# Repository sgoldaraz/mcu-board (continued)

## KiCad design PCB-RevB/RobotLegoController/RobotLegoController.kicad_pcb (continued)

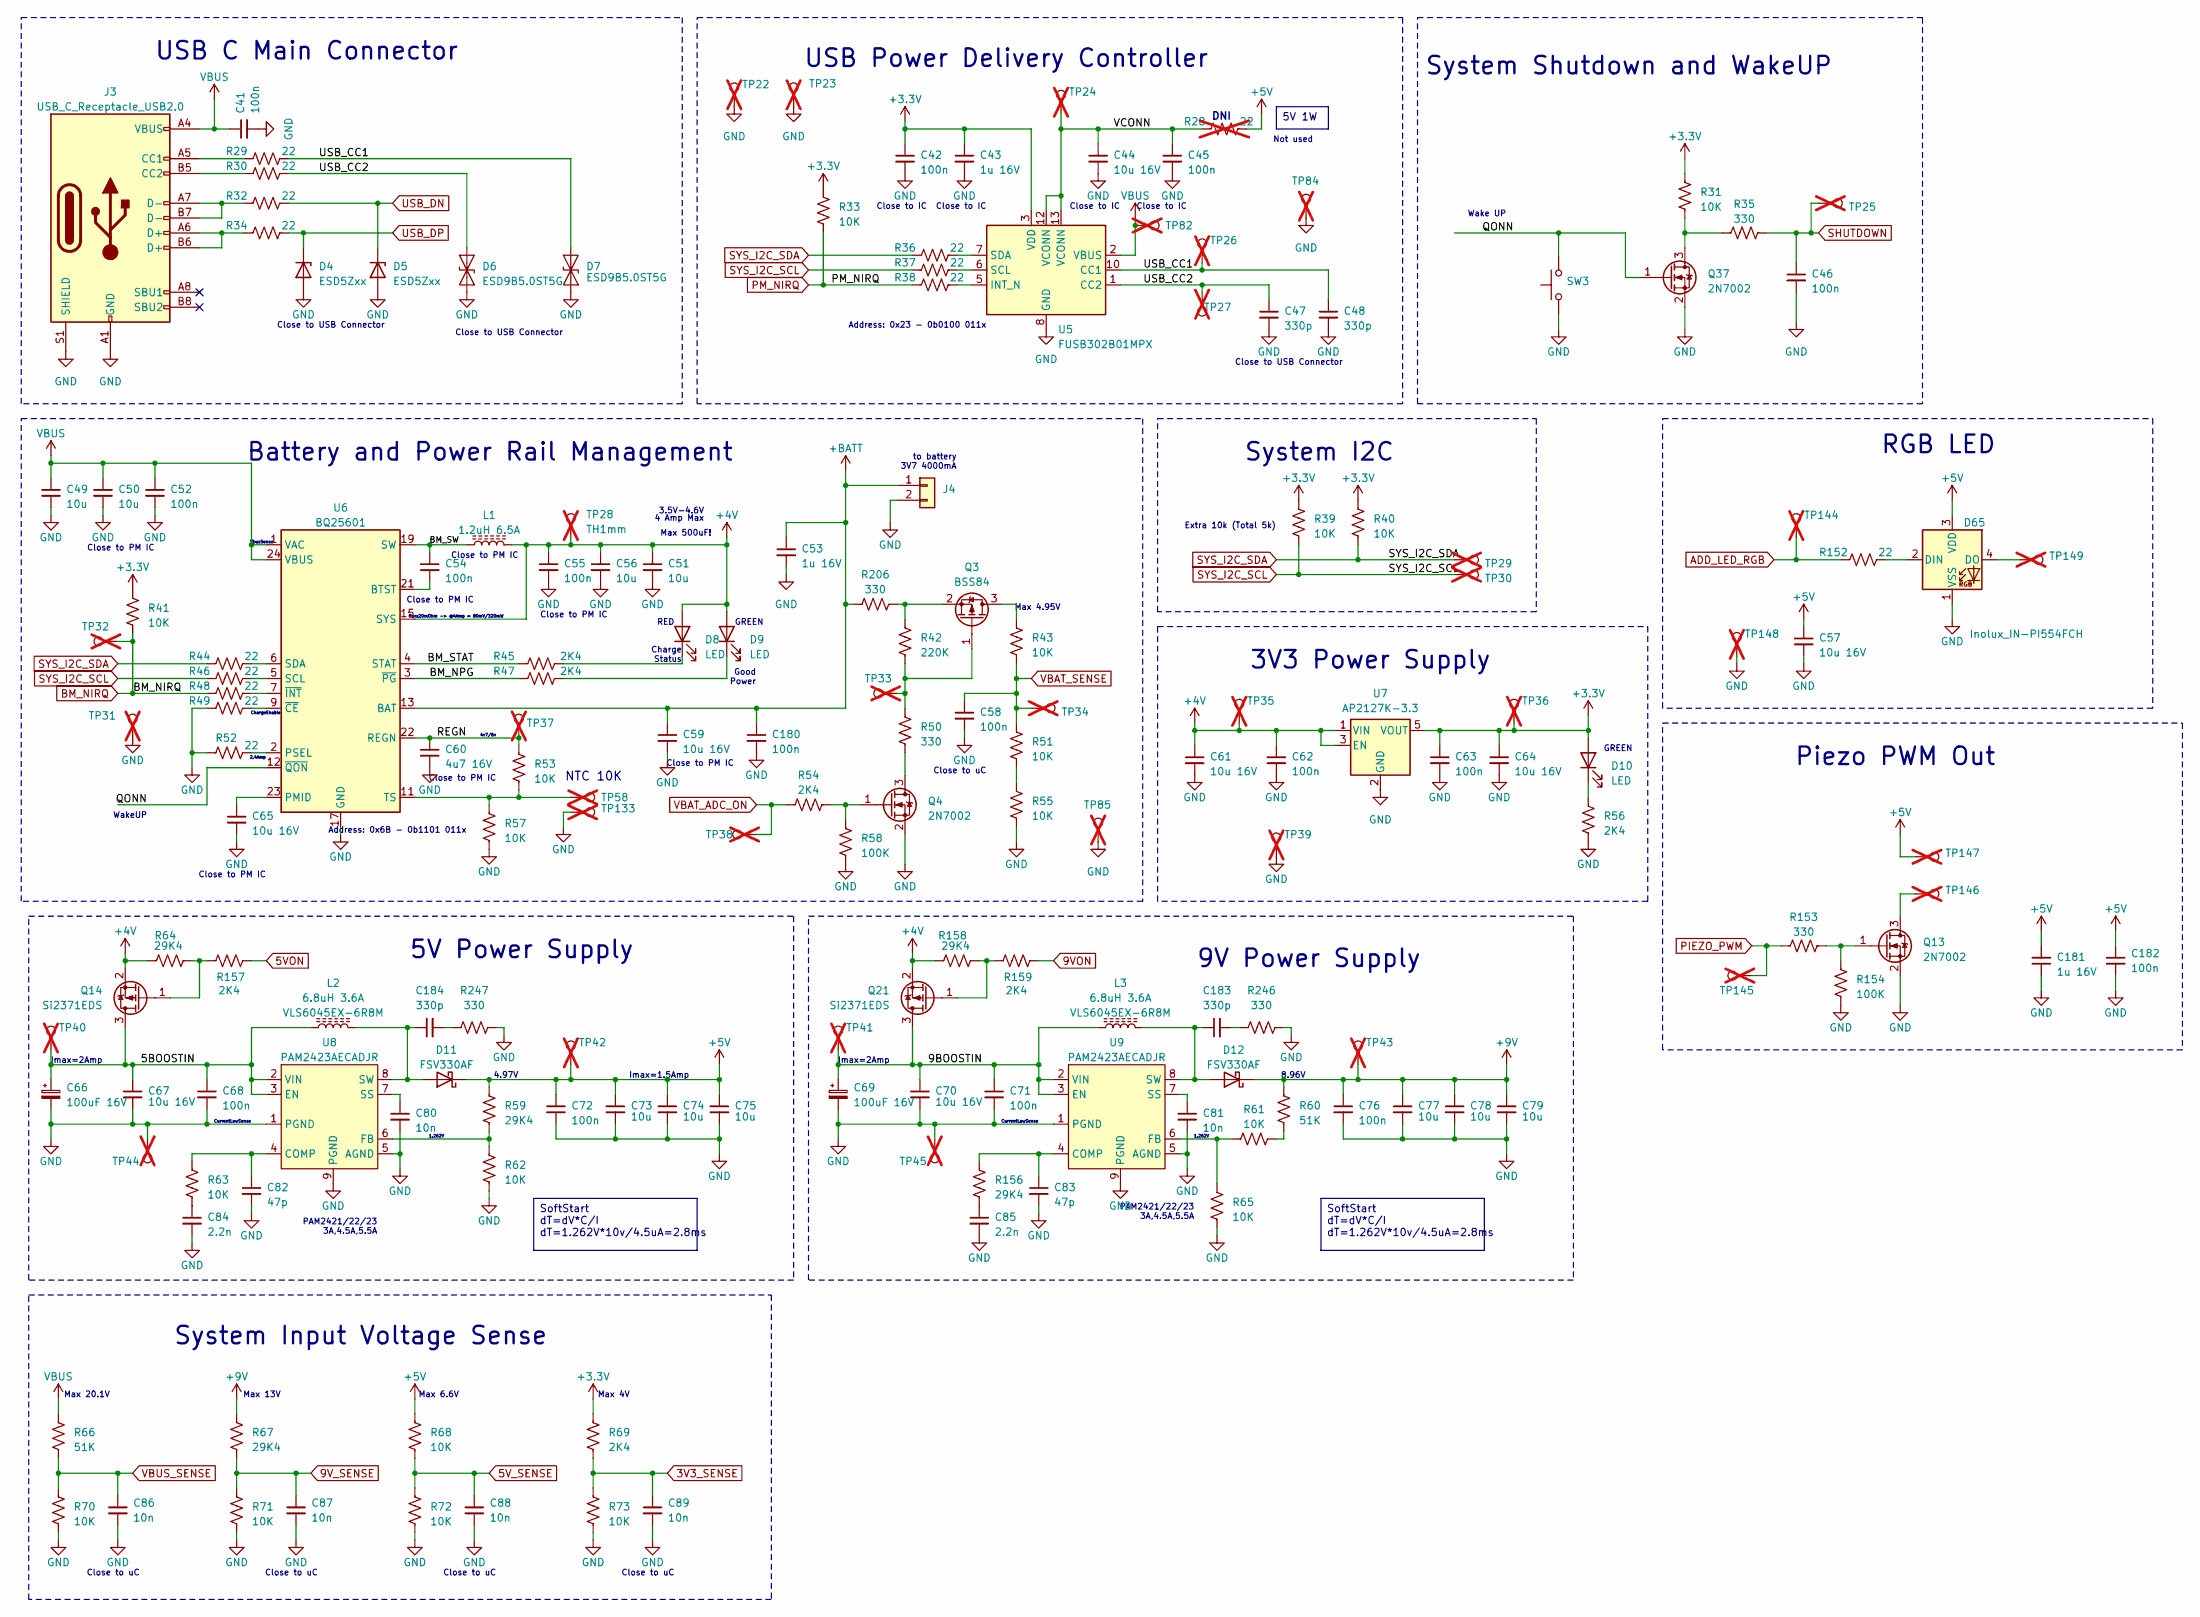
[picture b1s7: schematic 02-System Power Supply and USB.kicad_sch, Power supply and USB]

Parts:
C41, C42, C45, C46, C52, C54, C55, C58, C62, C63, C68, C71, C72, C76, C180, C182: 100n; C_0402_1005Metric
C43, C53, C181: 1u 16V; C_0603_1608Metric
C44, C57, C59, C61, C64, C65, C67, C70: 10u 16V; C_0805_2012Metric
C47, C48, C183, C184: 330p; C_0402_1005Metric
C49, C50, C51, C56, C73, C74, C75, C77, C78, C79: 10u; C_0805_2012Metric
C60: 4u7 16V; C_0603_1608Metric
C66, C69: 100uF 16V; CP_Elec_6.3x5.2
C80, C81, C86, C87, C88, C89: 10n; C_0402_1005Metric
C82, C83: 47p; C_0402_1005Metric
C84, C85: 2.2n; C_0402_1005Metric
D4, D5: ESD5Zxx; D_SOD-523
D6, D7: ESD9B5.0ST5G; D_SOD-923
D8, D9, D10: LED; LED_0402_1005Metric
D11, D12: FSV330AF; D_SOD-128
D65: Inolux_IN-PI554FCH; LED_Inolux_IN-PI554FCH_PLCC4_5.0x5.0mm_P3.2mm
J3: USB_C_Receptacle_USB2.0; USB_C_Receptacle_Palconn_UTC16-G
J4: Conn_01x02; JST_PH_B2B-PH-K_1x02_P2.00mm_Vertical
L1: 1.2uH 6.5A; L_Chilisin_BMRA00050520
L2, L3: 6.8uH 3.6A; L_Ferrocore_DLG-0504
Q3: BSS84; SOT-23
Q4, Q13, Q37: 2N7002; SOT-23
Q14, Q21: Si2371EDS; SOT-23
R28: 22; R_0402_1005Metric; not fitted
R29, R30, R32, R34, R36, R37, R38, R44, R46, R48, R49, R52, R152: 22; R_0402_1005Metric
R31, R33, R39, R40, R41, R43, R51, R53, R55, R57, R61, R62, R63, R65, R68, R70, R71, R72, R73: 10K; R_0402_1005Metric
R35, R50, R153, R206, R246, R247: 330; R_0402_1005Metric
R42: 220K; R_0402_1005Metric
R45, R47, R54, R56, R69, R157, R159: 2K4; R_0402_1005Metric
R58, R154: 100K; R_0402_1005Metric
R59, R64, R67, R156, R158: 29K4; R_0402_1005Metric
R60, R66: 51K; R_0402_1005Metric
SW3: SW_Omron_B3FS; SW_Push_1P1T_NO_6x6mm_H9.5mm
TP22, TP24, TP25, TP26, TP27, TP29, TP30, TP31, TP32, TP33, TP34, TP35, TP36, TP37, TP38, TP39, TP40, TP41, TP42, TP43, TP44, TP45, TP58, TP82, TP84, TP85, TP144, TP145, TP148: S1mm; TestPoint_Pad_1.0x1.0mm; not fitted
TP23, TP28, TP133, TP146, TP147, TP149: TH1mm; TestPoint_THTPad_1.0x1.0mm_Drill0.5mm; not fitted
U5: FUSB302B01MPX; WQFN-14-1EP_2.5x2.5mm_P0.5mm_EP1.45x1.45mm
U6: BQ25601; Texas_S-PWQFN-N24_EP2.7x2.7mm_ThermalVias
U7: AP2127K-3.3; SOT-23-5
U8, U9: PAM2423AECADJR; SOIC-8-1EP_3.9x4.9mm_P1.27mm_EP2.29x3mm_ThermalVias

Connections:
3V3_SENSE: C89.1, R69.1, R73.2; also elsewhere on the board
5VON: R157.1; also elsewhere on the board
5V_SENSE: C88.1, R68.1, R72.2; also elsewhere on the board
9VON: R159.1; also elsewhere on the board
9V_SENSE: C87.1, R67.1, R71.2; also elsewhere on the board
+3.3V: C42.1, C43.1, C63.1, C64.1, D10.2 (A), R31.2, R33.2, R39.2, R40.2, R41.2, R69.2, TP36.1, U5.3 (VDD), U5.4 (VDD), U7.5 (VOUT); also elsewhere on the board
+4V: C51.1, C55.1, C56.1, C61.1, C62.1, D8.2 (A), D9.2 (A), L1.2, Q14.2 (S), Q21.2 (S), R64.2, R158.2, TP28.1, TP35.1, U6.15 (SYS), U6.16 (SYS), U7.1 (VIN), U7.3 (EN)
+5V: C57.1, C72.1, C73.1, C74.1, C75.1, C181.2, C182.1, D11.1 (K), D65.3 (VDD), R28.2, R59.2, R68.2, TP42.1, TP147.1; also elsewhere on the board
+9V: C76.1, C77.1, C78.1, C79.1, D12.1 (K), R60.2, R67.2, TP43.1; also elsewhere on the board
+BATT: C53.1, C59.1, C180.1, J4.1, R206.1, U6.13 (BAT), U6.14 (BAT)
/02-System Power Supply and USB/5BOOSTIN: C66.1, C67.1, C68.1, L2.1, Q14.3 (D), TP40.1, U8.2 (VIN), U8.3 (EN)
/02-System Power Supply and USB/9BOOSTIN: C69.1, C70.1, C71.1, L3.1, Q21.3 (D), TP41.1, U9.2 (VIN), U9.3 (EN)
/02-System Power Supply and USB/BM_NPG: R47.1, U6.3 (~PG)
/02-System Power Supply and USB/BM_STAT: R45.1, U6.4 (STAT)
/02-System Power Supply and USB/BM_SW: C54.1, L1.1, U6.19 (SW), U6.20 (SW)
/02-System Power Supply and USB/QONN: Q37.1 (G), SW3.2, U6.12 (~QON)
/02-System Power Supply and USB/REGN: C60.1, R53.2, TP37.1, U6.22 (REGN)
/02-System Power Supply and USB/USB_CC1: C48.1, D7.2 (A2), R29.2, TP26.1, U5.10 (CC1), U5.11 (CC1)
/02-System Power Supply and USB/USB_CC2: C47.1, D6.2 (A2), R30.2, TP27.1, U5.1 (CC2), U5.14 (CC2)
/02-System Power Supply and USB/VCONN: C44.1, C45.1, R28.1, TP24.1, U5.12 (VCONN), U5.13 (VCONN)
ADD_LED_RGB: R152.1, TP144.1; also elsewhere on the board
BM_NIRQ: R41.1, R48.1, TP32.1; also elsewhere on the board
GND: C41.2, C42.2, C43.2, C44.2, C45.2, C46.2, C47.2, C48.2, C49.2, C50.2, C51.2, C52.2, C53.2, C55.2, C56.2, C57.2, C58.2, C59.2, C60.2, C61.2, C62.2, C63.2, C64.2, C65.2, C66.2, C67.2, C68.2, C69.2, C70.2, C71.2, C72.2, C73.2, C74.2, C75.2, C76.2, C77.2, C78.2, C79.2, C80.2, C81.2, C82.2, C83.2, C84.2, C85.2, C86.2, C87.2, C88.2, C89.2, C180.2, C181.1, C182.2, D4.2 (A), D5.2 (A), D6.1 (A1), D7.1 (A1), D65.1 (VSS), J3.A1 (GND), J3.A12 (GND), J3.B1 (GND), J3.B12 (GND), J3.S1 (SHIELD), J4.2, Q4.2 (S), Q13.2 (S), Q37.2 (S), R49.1, R52.1, R55.1, R56.1, R57.1, R58.1, R62.1, R65.1, R70.1, R71.1, R72.1, R73.1, R154.1, R246.2, R247.2, SW3.1, TP22.1, TP23.1, TP31.1, TP39.1, TP44.1, TP45.1, TP84.1, TP85.1, TP133.1, TP148.1, U5.8 (GND), U5.9 (GND), U5.15 (GND), U6.17 (GND), U6.18 (GND), U6.25 (GND), U7.2 (GND), U8.1 (PGND), U8.5 (AGND), U8.9 (PGND), U9.1 (PGND), U9.5 (AGND), U9.9 (PGND); also elsewhere on the board
unnamed: C84.1, R63.1
unnamed: C85.1, R156.1
unnamed: C183.2, R246.1
unnamed: C184.2, R247.1
unnamed: D8.1 (K), R45.2
unnamed: D9.1 (K), R47.2
unnamed: D10.1 (K), R56.2
unnamed: C184.1, D11.2 (A), L2.2, U8.8 (SW)
unnamed: C183.1, D12.2 (A), L3.2, U9.8 (SW)
unnamed: D65.2 (DIN), R152.2
unnamed: D65.4 (DO), TP149.1
unnamed: J3.A5 (CC1), R29.1
unnamed: J3.B5 (CC2), R30.1
unnamed: J3.A6 (D+), J3.B6 (D+), R34.1
unnamed: J3.A7 (D-), J3.B7 (D-), R32.1
unnamed: Q3.3 (D), R43.2
unnamed: Q3.1 (G), R42.2, R50.1, TP33.1
unnamed: Q3.2 (S), R42.1, R206.2
unnamed: Q4.3 (D), R50.2
unnamed: Q4.1 (G), R54.2, R58.2
unnamed: Q13.3 (D), TP146.1
unnamed: Q13.1 (G), R153.1, R154.2
unnamed: Q14.1 (G), R64.1, R157.2
unnamed: Q21.1 (G), R158.1, R159.2
unnamed: Q37.3 (D), R31.1, R35.2
unnamed: R51.1, R55.2
unnamed: R60.1, R61.1
unnamed: R38.2, U5.5 (INT_N)
unnamed: R37.2, U5.6 (SCL)
unnamed: R36.2, U5.7 (SDA)
unnamed: C54.2, U6.21 (BTST)
unnamed: C65.1, U6.23 (PMID)
unnamed: R52.2, U6.2 (PSEL)
unnamed: R46.2, U6.5 (SCL)
unnamed: R44.2, U6.6 (SDA)
unnamed: R53.1, R57.2, TP58.1, U6.11 (TS)
unnamed: R49.2, U6.9 (~CE)
unnamed: R48.2, U6.7 (~INT)
unnamed: C82.1, R63.2, U8.4 (COMP)
unnamed: R59.1, R62.2, U8.6 (FB)
unnamed: C80.1, U8.7 (SS)
unnamed: C83.1, R156.2, U9.4 (COMP)
unnamed: R61.2, R65.2, U9.6 (FB)
unnamed: C81.1, U9.7 (SS)
PIEZO_PWM: R153.2, TP145.1; also elsewhere on the board
PM_NIRQ: R33.1, R38.1; also elsewhere on the board
SHUTDOWN: C46.1, R35.1, TP25.1; also elsewhere on the board
SYS_I2C_SCL: R37.1, R39.1, R46.1, TP30.1; also elsewhere on the board
SYS_I2C_SDA: R36.1, R40.1, R44.1, TP29.1; also elsewhere on the board
USB_DN: D5.1 (K), R32.2; also elsewhere on the board
USB_DP: D4.1 (K), R34.2; also elsewhere on the board
VBAT_ADC_ON: R54.1, TP38.1; also elsewhere on the board
VBAT_SENSE: C58.1, R43.1, R51.2, TP34.1; also elsewhere on the board
VBUS: C41.1, C49.1, C50.1, C52.1, J3.A4 (VBUS), J3.A9 (VBUS), J3.B4 (VBUS), J3.B9 (VBUS), R66.2, TP82.1, U5.2 (VBUS), U6.1 (VAC), U6.24 (VBUS)
VBUS_SENSE: C86.1, R66.1, R70.2; also elsewhere on the board

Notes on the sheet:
3.5V-4.6V
System I2C
Close to PM IC
Imax=2Amp
Charge Status
Imax=1.5Amp
RGB LED
4.97V
Ron:20mOhm -> @4Amp = 80mV/320mW
Close to uC
USB Power Delivery Controller
Close to USB Connector
PAM2421/22/23 3A,4.5A,5.5A
Max 20.1V
Close to IC
Max 6.6V
ChargeEnable
Not used
Max 4.95V
VbusSense
9V Power Supply
WakeUP
Address: 0x6B - 0b1101 011x
2.4Amp
to battery 3V7 4000mA
System Input Voltage Sense
1.262V
5V Power Supply
4 Amp Max
USB C Main Connector
Max 13V
4v7/6v
System Shutdown and WakeUP
DNI
Address: 0x23 - 0b0100 011x
CurrentLowSense
NTC 10K
Piezo PWM Out
3V3 Power Supply
RED

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
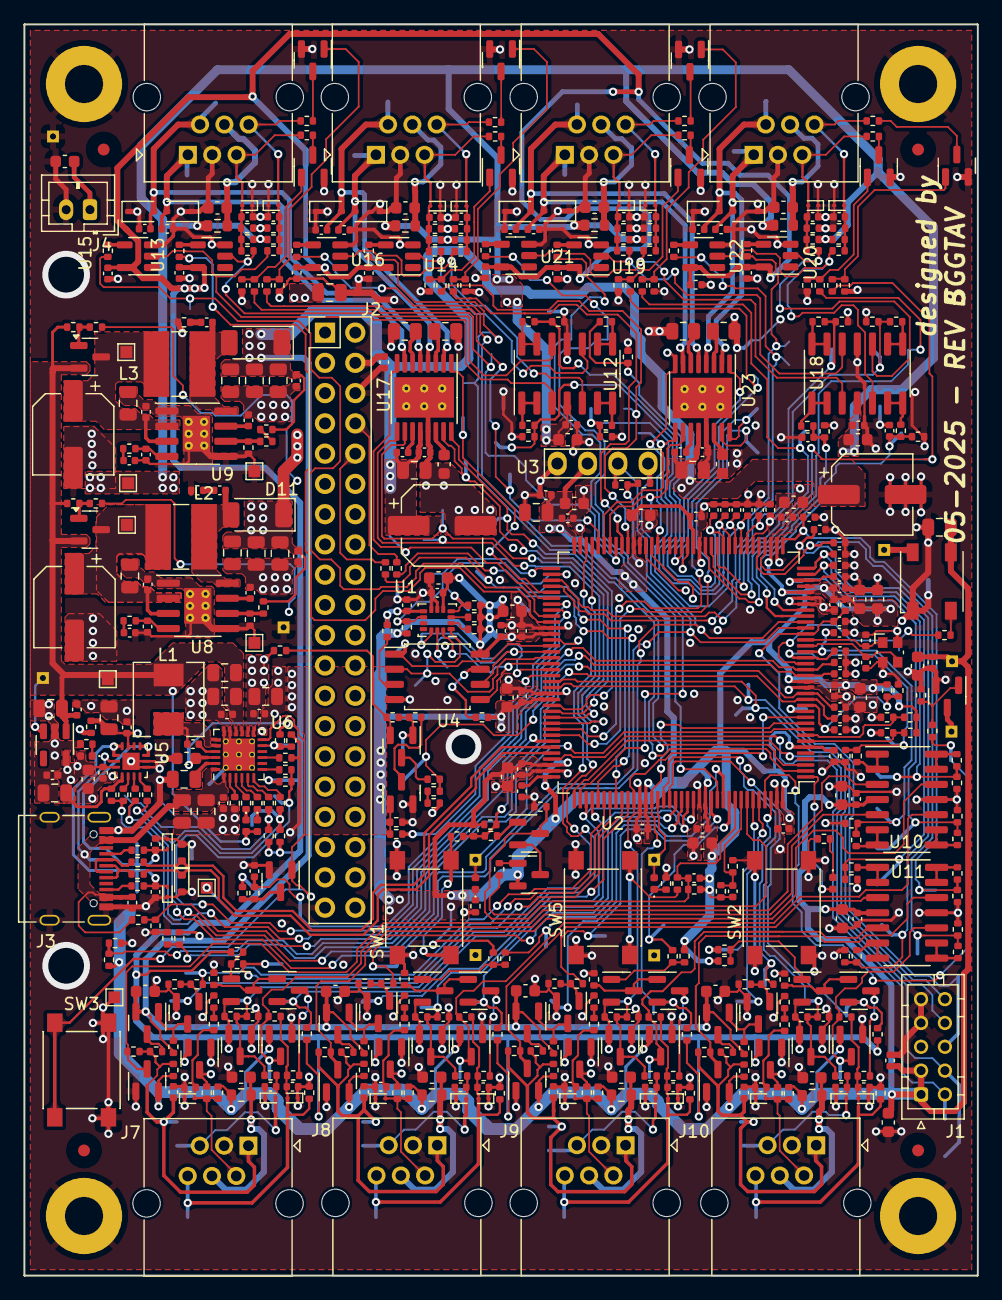
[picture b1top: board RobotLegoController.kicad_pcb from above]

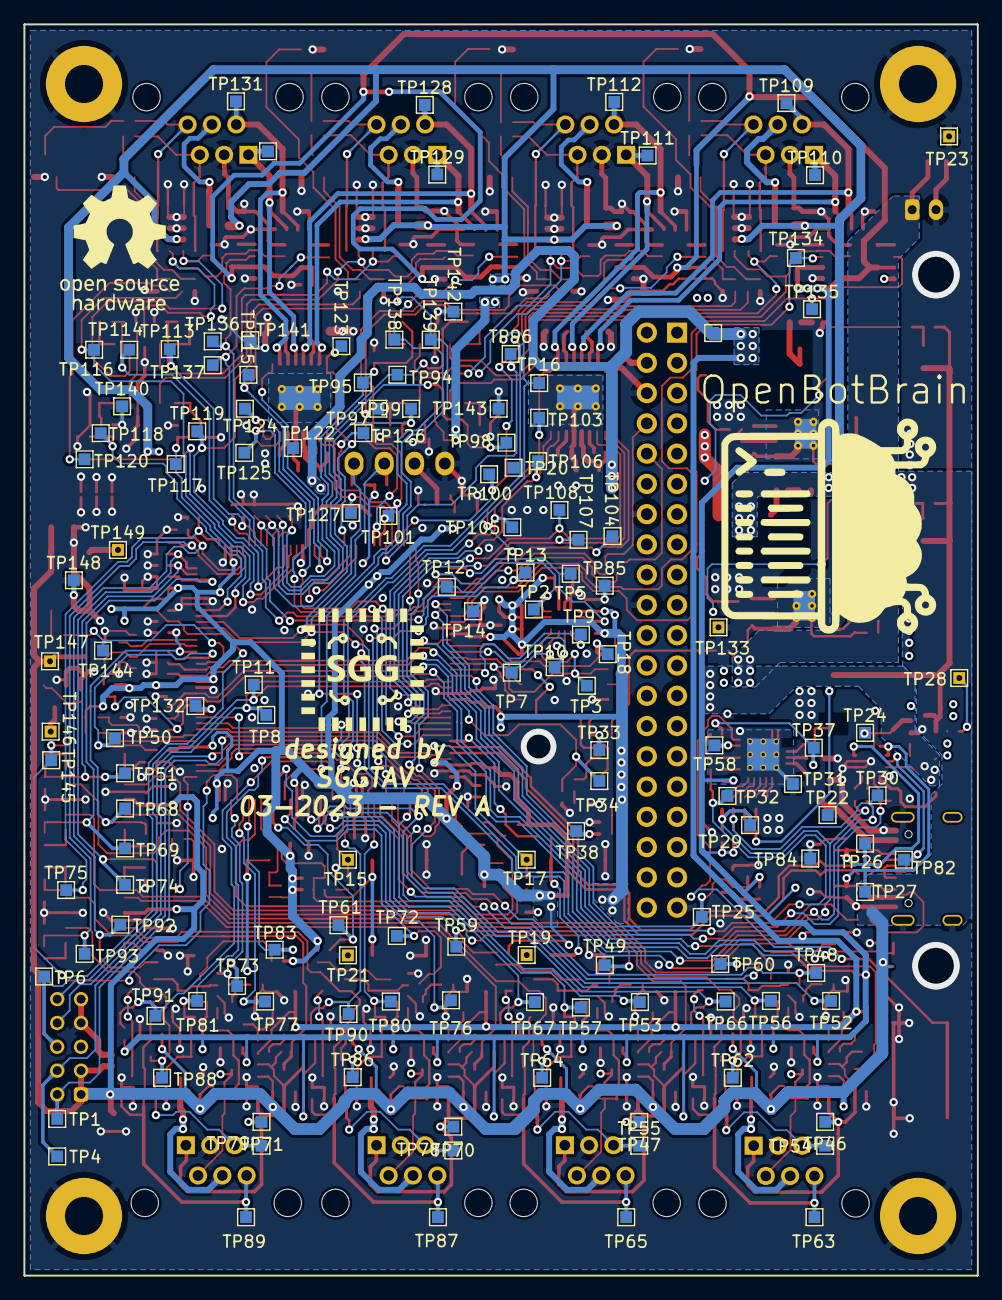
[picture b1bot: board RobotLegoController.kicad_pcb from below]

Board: 4 copper layers, 80.0 x 105.0 mm, 733 parts (142 on the bottom side), 315 nets.

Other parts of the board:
C133, C134, C138, C139: 10n; C_0402_1005Metric
R241, R244, R248, R249: 4K7; R_0402_1005Metric

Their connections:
/05-System Outputs A/MOTORA_PIN5: R241.1; also elsewhere on the board
/05-System Outputs A/MOTORA_PIN6: R244.1; also elsewhere on the board
/05-System Outputs A/MOTORB_PIN5: R249.1; also elsewhere on the board
/05-System Outputs A/MOTORB_PIN6: R248.1; also elsewhere on the board
GND: C133.2, C134.2, C138.2, C139.2; also elsewhere on the board

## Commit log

2025-04-13 Add rev b support. Initial copy
2025-04-25 Add rev A schematic
2025-04-26 Finish updating schematic REV B
2025-04-26 More pcb routing for rev b
2025-04-26 Alignment of the top connectors
2025-05-04 More work on pcb layout
2025-05-05 More output layout done
2025-05-05 Finish with the pcb layout.
